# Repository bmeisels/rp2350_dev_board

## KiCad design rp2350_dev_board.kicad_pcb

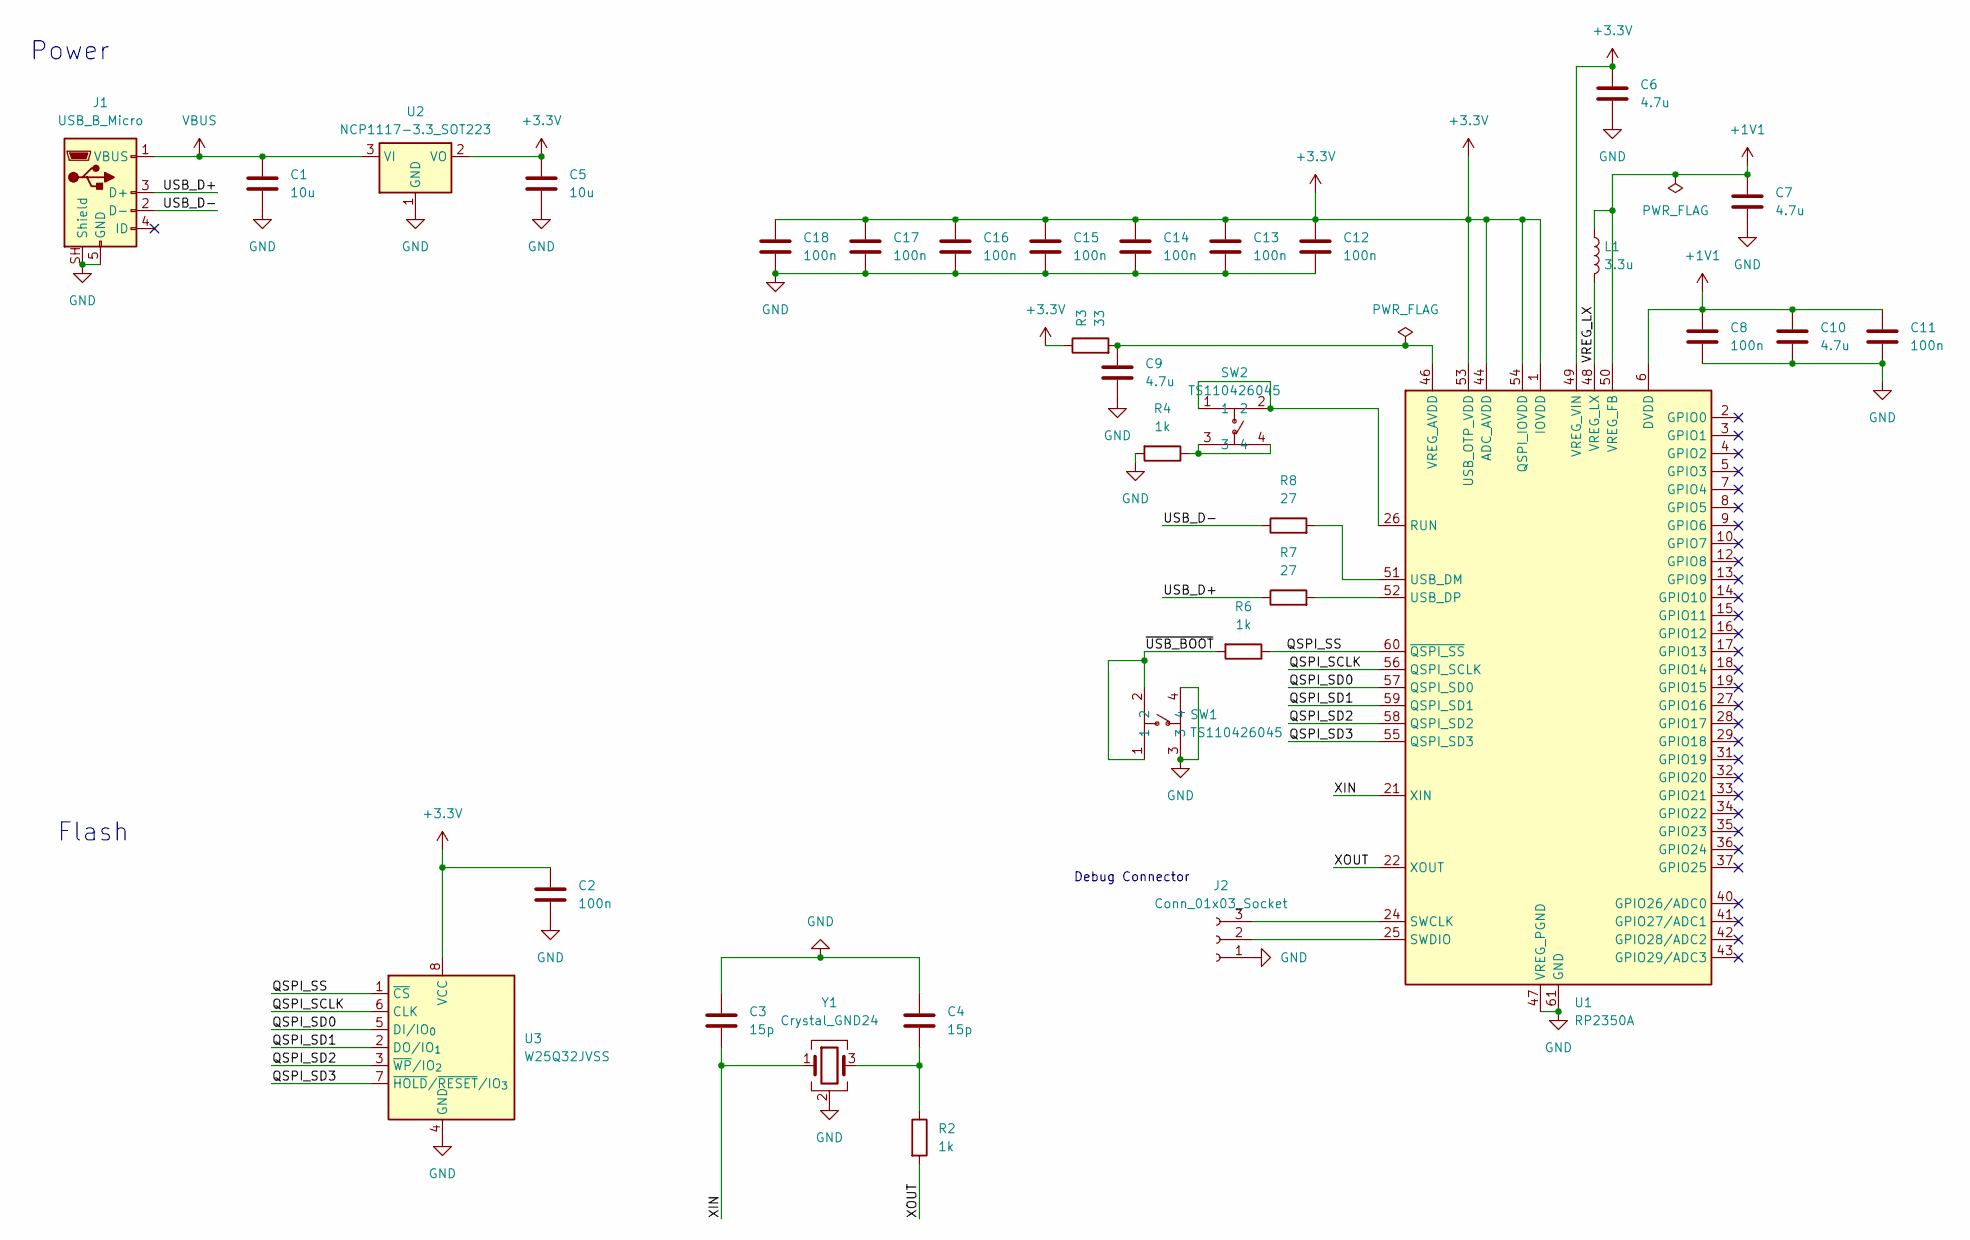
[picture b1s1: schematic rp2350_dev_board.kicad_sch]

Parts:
C1, C5: 10u; C_0402_1005Metric
C2, C8, C11, C12, C13, C14, C15, C16, C17, C18: 100n; C_0402_1005Metric
C3, C4: 15p; C_0402_1005Metric
C6, C7: 4.7u; C_0402_1005Metric_small_pads
C9, C10: 4.7u; C_0402_1005Metric
J1: USB_B_Micro; USB_Micro-B_Amphenol_10103594-0001LF_Horizontal
J2: Conn_01x03_Socket; PinSocket_1x03_P2.54mm_Vertical
L1: 3.3u; L_pol_2016
R2, R4, R6: 1k; R_0402_1005Metric
R3: 33; R_0402_1005Metric
R7, R8: 27; R_0402_1005Metric
SW1, SW2: TS110426045; SW-SMD_4P-L6.0-W6.0-P4.50-LS9.0-2; LCSC Part C22375341
U1: RP2350A; QFN-60-1EP_7x7mm_P0.4mm_EP3.4x3.4mm
U2: NCP1117-3.3_SOT223; SOT-223-3_TabPin2
U3: W25Q32JVSS; SOIC-8_5.3x5.3mm_P1.27mm
Y1: Crystal_GND24; Crystal_SMD_3225-4Pin_3.2x2.5mm

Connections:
+1V1: C7.1, C8.2, C10.2, C11.2, L1.1, U1.6 (DVDD), U1.23 (DVDD), U1.39 (DVDD), U1.50 (VREG_FB)
+3.3V: C2.1, C5.1, C6.1, C12.2, C13.2, C14.2, C15.2, C16.2, C17.2, C18.2, R3.1, U1.1 (IOVDD), U1.11 (IOVDD), U1.20 (IOVDD), U1.30 (IOVDD), U1.38 (IOVDD), U1.44 (ADC_AVDD), U1.45 (IOVDD), U1.49 (VREG_VIN), U1.53 (USB_OTP_VDD), U1.54 (QSPI_IOVDD), U2.2 (VO), U3.8 (VCC)
/QSPI_SCLK: U1.56 (QSPI_SCLK), U3.6 (CLK)
/QSPI_SD0: U1.57 (QSPI_SD0), U3.5 (DI/IO_{0})
/QSPI_SD1: U1.59 (QSPI_SD1), U3.2 (DO/IO_{1})
/QSPI_SD2: U1.58 (QSPI_SD2), U3.3 (~WP/IO_{2})
/QSPI_SD3: U1.55 (QSPI_SD3), U3.7 (~HOLD/~RESET/IO_{3})
/QSPI_SS: R6.1, U1.60 (~QSPI_SS), U3.1 (~CS)
/USB_D+: J1.3 (D+), R7.1
/USB_D-: J1.2 (D-), R8.1
/VREG_LX: L1.2, U1.48 (VREG_LX)
/XIN: C3.2, U1.21 (XIN), Y1.1
/XOUT: R2.2, U1.22 (XOUT)
/~USB_BOOT: R6.2, SW1.1, SW1.2
GND: C1.2, C2.2, C3.1, C4.1, C5.2, C6.2, C7.2, C8.1, C9.2, C10.1, C11.1, C12.1, C13.1, C14.1, C15.1, C16.1, C17.1, C18.1, J1.5 (GND), J1.SH (Shield), J2.1, R4.2, SW1.3, SW1.4, U1.47 (VREG_PGND), U1.61 (GND), U2.1 (GND), U3.4 (GND), Y1.2 (G), Y1.4 (G)
unnamed: C4.2, R2.1, Y1.3
unnamed: J2.2, U1.25 (SWDIO)
unnamed: J2.3, U1.24 (SWCLK)
unnamed: R4.1, SW2.3, SW2.4
unnamed: SW2.1, SW2.2, U1.26 (RUN)
unnamed: R8.2, U1.51 (USB_DM)
unnamed: R7.2, U1.52 (USB_DP)
unnamed: C9.1, R3.2, U1.46 (VREG_AVDD)
VBUS: C1.1, J1.1 (VBUS), U2.3 (VI)

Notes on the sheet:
Power
Debug Connector
Flash

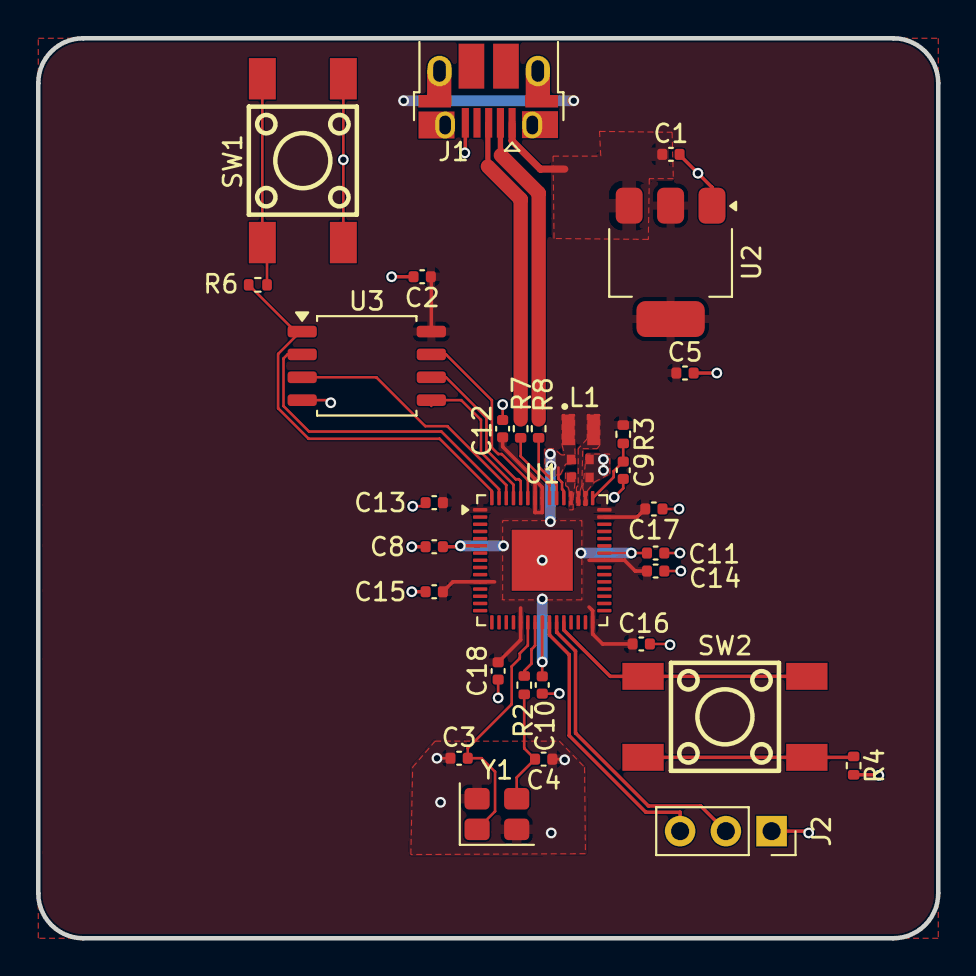
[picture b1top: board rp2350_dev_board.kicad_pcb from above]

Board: 2 copper layers, 50.0 x 50.0 mm, 33 parts (0 on the bottom side), 24 nets.

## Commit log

2026-05-17 Finished schematic
2026-05-24 Minimal board complete
2026-05-24 Add part numbers
